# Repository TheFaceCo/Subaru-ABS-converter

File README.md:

# Subaru-ABS-converter
Read hall sensors, output variable reluctance (VR) sensors.

This converts modern hall sensor inputs to older VR outputs using a Maxim 9921 IC to read 2-wire hall sensors with a Teensy 3.2. 
Use this device if you are installing new hubs that use hall wheel speed sensors on old cars with variable reluctance ABS tone-rings.

The output stage is a 2-bit digital output fed to an audio transformer (1:1 600ohm:600ohm). 
The transformer removes the DC bias and presents an inductive source to the OEM ABS inputs (to circumvent open- or short-circuit error detection).

Set the input wheel tooth count to the OEM VR wheel tooth count. 

Set the output wheel tooth count to 2x the number of magnetic poles (count poles using magentic film, see image of subaru encoder). 
The Max9921 counts both the rising and falling edge of each magnetic pole, hence the multiplier.

Set Teensy clock to 24MHz to reduce thermal issues. CPU may freeze at high temperatures. First suspect for stability problems is the crystal oscillator. 

This also includes a generic digital output labeled "VSS". This allows the device to present a VSS signal calculated as the average of both inputs.
The VSS output can be used to provide a VSS signal in the case of a new transmission without a built-in VSS sensor.
The VSS output, as installed in my car, just drives an LED and is used for status reporting. This needs to be modified if you want a proper VSS output.

There is an additional op-amp stage, but this has been left un-routed due to pure laziness. 

This setup produces and unknown amount of jitter, but it should be relatively small. 

Outputs will be disabled by >1 error per 10 seconds in the default config. 

Be sure to cut the USB power trace on the teensy prior to soldering to the board.

Use at your own risk.

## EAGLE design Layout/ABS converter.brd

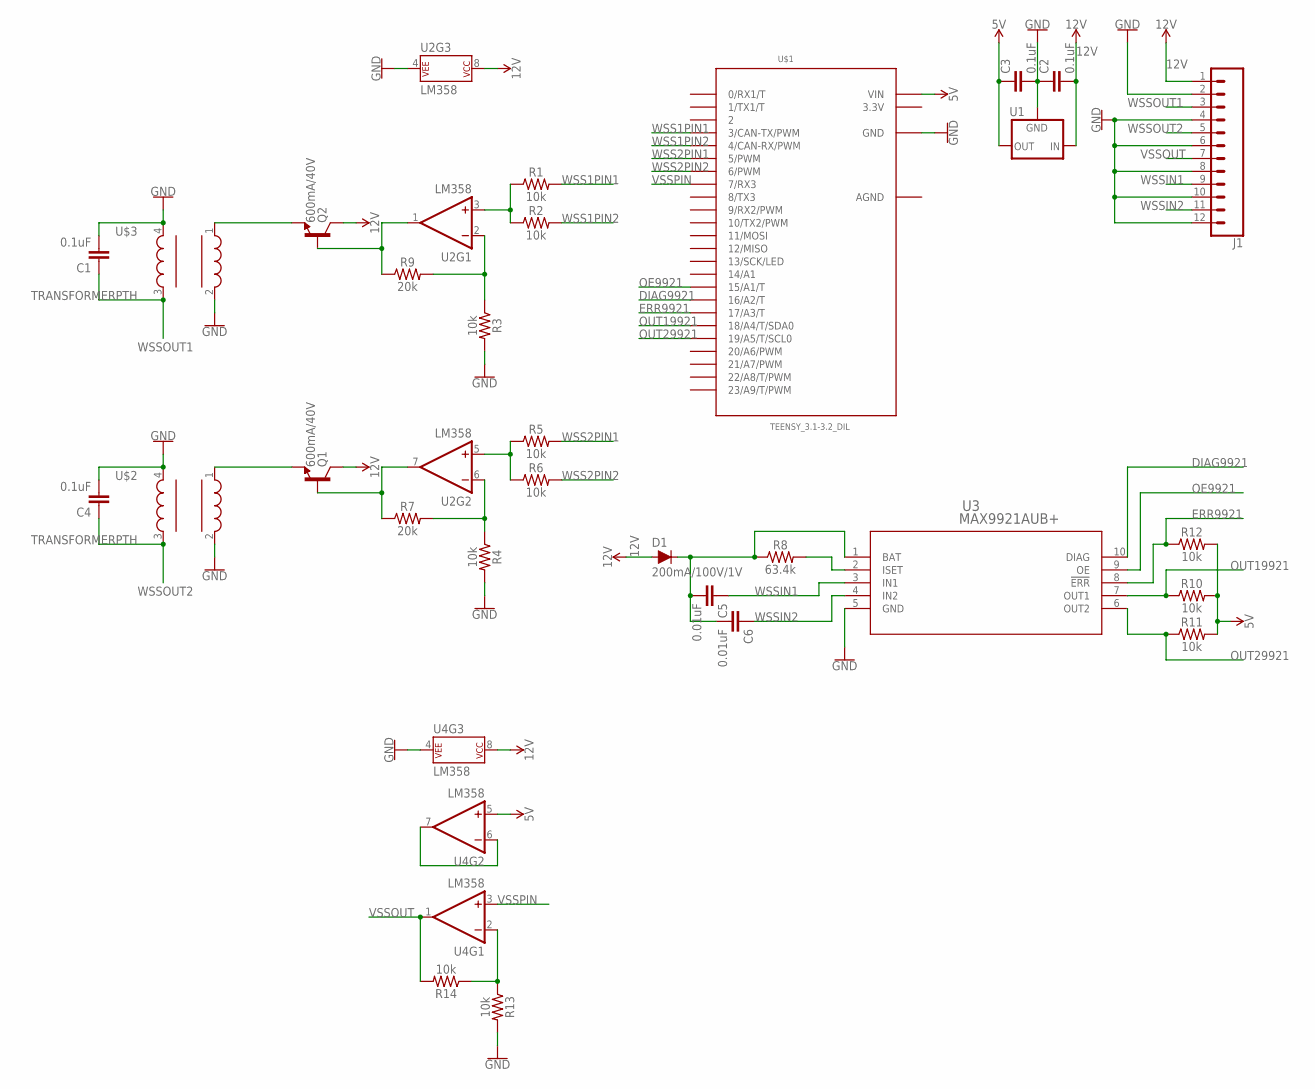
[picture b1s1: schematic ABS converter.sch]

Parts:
C1, C2, C3, C4: 0.1uF; CAP-PTH-SMALL-KIT
C5, C6: 0.01uF; CAP-PTH-SMALL-KIT
D1: 200mA/100V/1V; DIODE-1N4148
J1: CONN_12; 1X12
Q1, Q2: 600mA/40V; TO-92
R1, R2, R3, R4, R5, R6, R10, R11, R12, R13, R14: 10k; AXIAL-0.3
R7, R9: 20k; AXIAL-0.3
R8: 63.4k; AXIAL-0.3
U1: V_REG_78XX-TO-220; TO-220-ALT
U2, U4: LM358; DIP08
U3: MAX9921AUB+; 21-0061L
U$1: TEENSY_3.1-3.2_DIL; TEENSY_3.0-3.2&LC_DIL
U$2, U$3: TRANSFORMERPTH; TRANSFORMER

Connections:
3.3V: U$1.3.3V
5V: C3.1, R10.P$2 (2), R11.P$2 (2), R12.P$2 (2), U1.OUT, U4.5 (+IN), U$1.VIN
12V: C2.2, D1.A, J1.1, Q1.1 (C), Q2.1 (C), U1.IN, U2.8 (P$V+), U4.8 (P$V+)
AGND: U$1.AGND
DIAG9921: U3.10 (DIAG), U$1.16/A2 (16/A2/T)
ERR9921: R12.P$1 (1), U3.8 (!ERR), U$1.17/A3 (17/A3/T)
GND: C1.2, C2.1, C3.2, C4.2, J1.2, J1.4, J1.6, J1.8, J1.10, J1.12, R3.P$2 (2), R4.P$2 (2), R13.P$2 (2), U1.GND, U2.4 (P$V-), U3.5 (GND), U4.4 (P$V-), U$1.GND, U$2.2, U$2.4, U$3.2, U$3.4; also elsewhere on the board
unnamed: Q2.2 (B), R9.P$1 (1), U2.1 (OUT)
unnamed: R1.P$1 (1), R2.P$1 (1), U2.3 (+IN)
unnamed: R3.P$1 (1), R9.P$2 (2), U2.2 (-IN)
unnamed: Q2.3 (E), U$3.1
unnamed: R5.P$1 (1), R6.P$1 (1), U2.5 (+IN)
unnamed: R4.P$1 (1), R7.P$2 (2), U2.6 (-IN)
unnamed: Q1.2 (B), R7.P$1 (1), U2.7 (OUT)
unnamed: Q1.3 (E), U$2.1
unnamed: R8.P$2 (2), U3.2 (ISET)
unnamed 16: C5.2, C6.2, D1.C, R8.P$1 (1), U3.1 (BAT); also elsewhere on the board
unnamed: U4.6 (-IN), U4.7 (OUT)
unnamed: R13.P$1 (1), R14.P$1 (1), U4.2 (-IN)
OE9921: U3.9 (OE), U$1.15/A1 (15/A1/T)
OUT19921: R10.P$1 (1), U3.7 (OUT1), U$1.18/A4 (18/A4/T/SDA0)
OUT29921: R11.P$1 (1), U3.6 (OUT2), U$1.19/A5 (19/A5/T/SCL0)
VSSOUT: J1.7, R14.P$2 (2), U4.1 (OUT)
VSSPIN: U4.3 (+IN), U$1.7 (7/RX3)
WSS1PIN1: R1.P$2 (2), U$1.3 (3/CAN-TX/PWM)
WSS1PIN2: R2.P$2 (2), U$1.4 (4/CAN-RX/PWM)
WSS2PIN1: R5.P$2 (2), U$1.5 (5/PWM)
WSS2PIN2: R6.P$2 (2), U$1.6 (6/PWM)
WSSIN1: C5.1, J1.9, U3.3 (IN1)
WSSIN2: C6.1, J1.11, U3.4 (IN2)
WSSOUT1: C1.1, J1.3, U$3.3
WSSOUT2: C4.1, J1.5, U$2.3

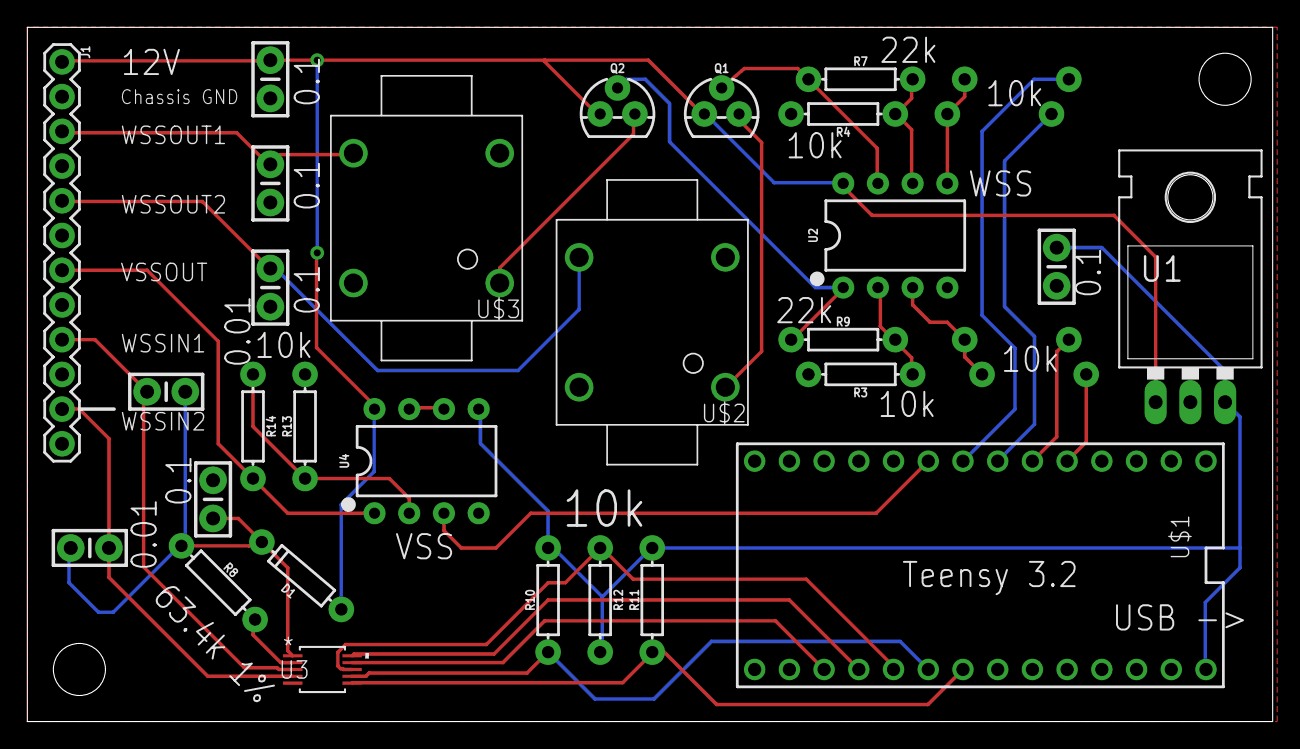
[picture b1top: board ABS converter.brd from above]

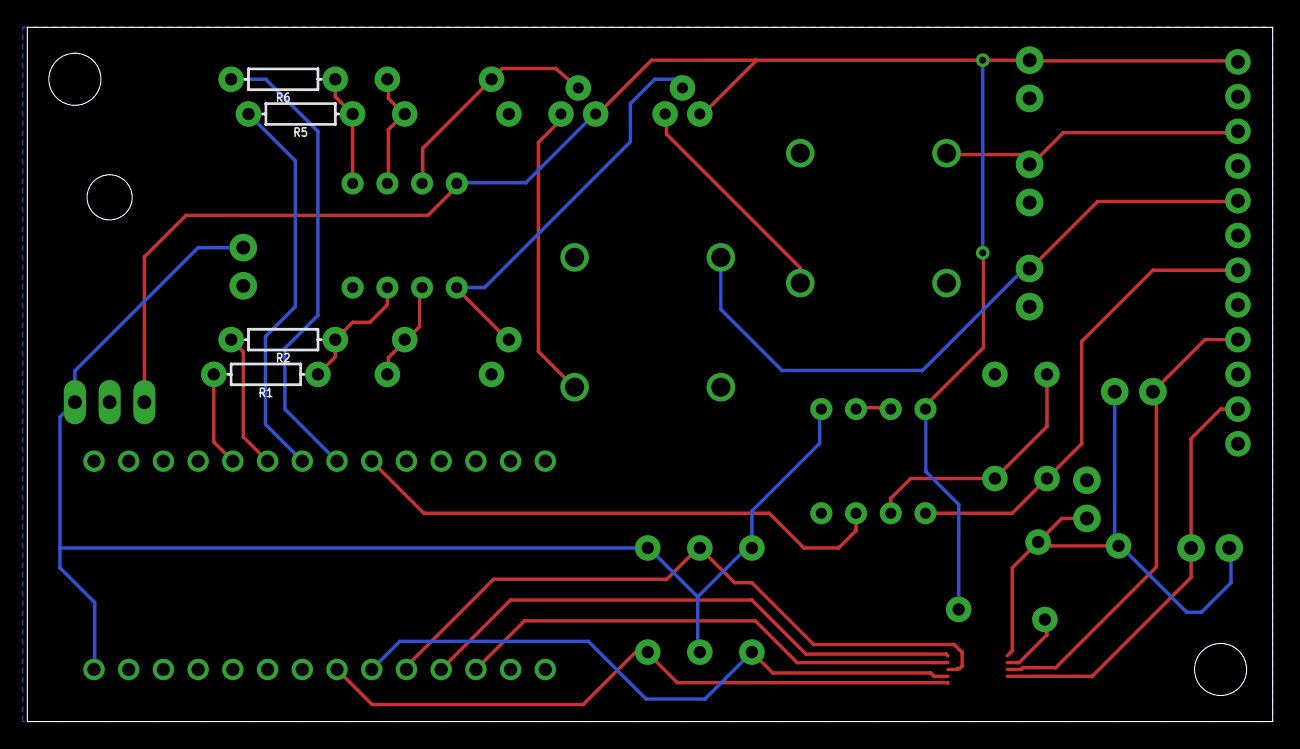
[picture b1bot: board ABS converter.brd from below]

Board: 2 copper layers, 91.1 x 50.8 mm, 32 parts (4 on the bottom side), 30 nets.

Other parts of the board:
C7: 0.1uF; CAP-PTH-SMALL-KIT

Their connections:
GND: C7.2; also elsewhere on the board
unnamed 16: C7.1; also elsewhere on the board

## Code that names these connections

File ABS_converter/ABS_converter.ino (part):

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const unsigned long outputwheelteeth = 44;
const unsigned long VSSwheelteeth = 1; //this number is made up. Set to correct wheel count from transmission

#define WSS1PIN1  3
#define WSS1PIN2  4
#define WSS2PIN1  5
#define WSS2PIN2  6
#define VSSPIN    7
#define OE9921    15
#define DIAG9921  16
#define ERR9921   17
#define OUT19921  18
#define OUT29921  19
#define ONBOARDLED 13

unsigned long halfwave = 300; //used to determined the shape of the output pulse
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
  //  }
  //wheelspeed outputs use two output pins through a voltage divider for 0, 1.75, and 3v (00, 01, and 11)
  pinMode(WSS1PIN1, OUTPUT); //wheelspeed 1 output 1
  pinMode(WSS1PIN2, OUTPUT); //wheelspeed 1 output 2
  pinMode(WSS2PIN1, OUTPUT);//wheelspeed 2 output 1
  pinMode(WSS2PIN2, OUTPUT);//wheelspeed 2 output 2

  pinMode(VSSPIN, OUTPUT);//VSS output
  pinMode(OE9921, OUTPUT);//Output enable to MAX9921
  pinMode(DIAG9921, OUTPUT);//Diag to MAX9921
  pinMode(ERR9921, INPUT); //ERR from MAX9921
  pinMode(OUT19921, INPUT); //Hall 1 signal from MAX9921
  pinMode(OUT29921, INPUT); //Hall 2 signal from MAX9921

  pinMode(ONBOARDLED, OUTPUT); //onboard LED to display power
  digitalWriteFast(ONBOARDLED, HIGH); //display power state
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
  Serial.println("Max9921 enabled");

  attachInterrupt(digitalPinToInterrupt(OUT19921), input1ISR, CHANGE); //count rising and falling edges of Max9921 outputs.
  attachInterrupt(digitalPinToInterrupt(OUT29921), input2ISR, CHANGE);
  attachInterrupt(digitalPinToInterrupt(ERR9921), ERRISR, FALLING);

  delayflag1 = micros(); //sets up initial conditions for WSS output waveform
  periodflag1 = delayflag1; //avoid second call to micros(), trickrepeated throughout
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
  VSSdelayflag = delayflag1;

  digitalWriteFast(WSS1PIN1, HIGH);
  digitalWriteFast(WSS1PIN2, LOW);
  digitalWriteFast(WSS2PIN1, HIGH);
  digitalWriteFast(WSS2PIN2, LOW);
  digitalWriteFast(VSSPIN, HIGH);

  updateVSS();
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      //    if (period1 > minimumspeed) {
      if (periodtimer1 - delayflag1 >= signal1start) {
        if (!signal1started) {
          digitalWriteFast(WSS1PIN1, LOW);
          digitalWriteFast(WSS1PIN2, LOW);
          signal1started = true;
          signal1send = signal1start + halfwave; //re-find zero crossing center in order to tolerate rapidly changing periods. If this is preloaded, signal distortion will result when the period is updated at a bad time.
          signal1end = signal1send + halfwave; //re-find waveform end (should correspond to the period on average)
        }
        if (!signal1sent) {
          if (periodtimer1 - delayflag1 >= signal1send) {
            digitalWriteFast(WSS1PIN1, HIGH);
            digitalWriteFast(WSS1PIN2, HIGH);
            signal1sent = true;
            signal1ended = false;
          }
        }
        if (!signal1ended) {
          if (periodtimer1 - delayflag1 >= signal1end) {
            digitalWriteFast(WSS1PIN1, HIGH);
            digitalWriteFast(WSS1PIN2, LOW);
            delayflag1 = periodtimer1;
            signal1ended = true;
            signal1started = false;
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      }
      //    }
      //    else {
      //      digitalWriteFast(WSS1PIN1, HIGH);
      //      digitalWriteFast(WSS1PIN2, LOW);
      //      delayflag1 = periodtimer1;
      //      signal1ended = true;
      //      signal1started = false;
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      //    if (period2 > minimumspeed) {
      if (periodtimer2 - delayflag2 >= signal2start) {
        if (!signal2started) {
          digitalWriteFast(WSS2PIN1, LOW);
          digitalWriteFast(WSS2PIN2, LOW);
          signal2started = true;
          signal2send = signal2start + halfwave; //re-find zero crossing center in order to tolerate rapidly changing periods. If this is preloaded, signal distortion will result when the period is updated at a bad time.
          signal2end = signal2send + halfwave; //re-find waveform end (should correspond to the period on average)
        }
        if (!signal2sent) {
          if (periodtimer2 - delayflag2 >= signal2send) {
            digitalWriteFast(WSS2PIN1, HIGH);
            digitalWriteFast(WSS2PIN2, HIGH);
            signal2sent = true;
            signal2ended = false;
          }
        }
        if (!signal2ended) {
          if (periodtimer2 - delayflag2 >= signal2end) {
            digitalWriteFast(WSS2PIN1, HIGH);
            digitalWriteFast(WSS2PIN2, LOW);
            delayflag2 = periodtimer2;
            signal2ended = true;
            signal2started = false;
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      }
      //    }
      //    else {
      //      digitalWriteFast(WSS2PIN1, HIGH);
      //      digitalWriteFast(WSS2PIN2, LOW);
      //      delayflag2 = periodtimer2;
      //      signal2ended = true;
      //      signal2started = false;
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    }
  }
  if (errreport > 1) { //if more than 1 error has been encountered in 10 seconds disable outputs and write error out to LED connected to VSS pin.
    detachInterrupt(digitalPinToInterrupt(ERR9921));
    disabled = true; //
    if (!VSSoutput) { //if the VSS pin is used for a status LED, use it to blink the most recent error reported by Max9921. One blink = 0, two blinks = 1
      for (int i = 0; i <= 5; i++) {
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}

void ERRISR() {
  digitalWriteFast(DIAG9921, HIGH); //drive diagnostic pin high to retreive diagnostic info. See truth table in Max9921 documentation. IN1 faults mask IN2 faults. Faults are transient (not latched), so this must be fast.
  delayMicroseconds(1); //allow a bit of time for error output. 350ns according to Max9921 documentation. This probably isn't required, but it's hard to say.
  ERRstatus = digitalReadFast(ERR9921); //Retrieve pin status
  OUT1status = digitalReadFast(OUT19921);
  OUT2status = digitalReadFast(OUT29921);
  digitalWriteFast(DIAG9921, LOW); //drive diagnostic pin low to reset faulted sensor.
  error = true;
}

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
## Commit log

2019-08-29 made a housing for it
2019-08-29 fixed component heights
2019-08-29 tooth count images
2019-08-31 added corrected tone ring tooth counts
    -
2019-09-16 fixed resistor labels
    changes to common 22k from 20k on opamps. Added big label to 63.4k resistor for max9921 chip configuration.
2019-09-16 Updated for correct pinouts
    Added temporary VSS output. Split out inputs and outputs for L/R WSS.
    Added some more labels on board and moved them around for visibility when assembled.
2019-09-17 removed input filter
    changed some other things that were inconsequential.
    ABS light goes off, but ABS is super sensitive, suggesting that the period conversion is wrong.
2019-09-17 simplified slightly
    set a couple settings back to originals
2019-09-17 set rolling average to 50/50 factors
2019-09-17 rejigger to lock out period updates during waveform generation
2019-09-18 added back in the filter, block operation until a WSS sees an input.
2019-09-18 added minimum speed to outputs
    inverted output waveform
2019-09-18 what the fuck
    inverted the tooth counts and the brakes work properly, but not with the number in the correct spot.
2019-09-20 --- This seems to work ---
    set output tooth count to 88 (presumably there is a logic inverter to get a second pulse between teeth?).
    Seems sensitive to pulsewidth. 600uS seems like a happy medium - 400 uS seems to throw a light eventually and 750uS seems to throw a light quickly.
    Changed complements to 90/10 from 50/50. Changed light timeout to 2000 pulses.
    Could change to timeout at 300,000,000uS to get a 5 minute delay or 120,000,000 to get a 2 minute delay.
    Expect extreme jitter around 90mph with this code, due to the 600uS pulse running out of time (need 425uS pulsewidth at 120mph).
2019-09-20 changed to do math all the time
    Does the period update at all times, but doesn't shunt the result into the active variable until it's outside the waveform.
    Compresses waveform to 400uS when period is less than 650uS.
2019-09-20 changed to period variable scaling
    Changed from fixed period scaling to dynamic period scaling in order to keep wavelength as long as practicable. Scaling starts around 85mph (18.9 rev/s at 808 revs/mile)
2019-09-20 Update ABS_converter.ino
    added VSS light count to declarations
2019-09-20 figured out the math problem.
    the hall sensor is probably only reading every other encoder line, due to being a 2-wire hall sensor. Need to read up on how exactly they work.
2019-09-20 fixed lack of explicit outpu on diag port
2019-09-20 regr
2019-09-20 documentation
    etc
2019-09-20 debug to verify count of 48 input teeth
    turns out alternating poles meants 96 on the magnet paper is 48 electrical.
2019-09-20 ISR's to 'change'
    The encoder alternates magnetic poles, and the max9921 interprets them as 1-0-1-0-etc. Both rising and falling edges are mechanically precise, and using both will reduce the output latency (since you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
    Filter changed to weight the previous value more heavily as a resut.
2019-09-20 Add VSS on/off selection, cleaned up variable definitions
    added filter back to VSS output.
2019-09-20 photos
2020-08-30 added diagnostic output to VSS pin
    As installed in my car, the VSS pin is being used to drive an LED. This outputs some diagnostics over the LED pin and serial.
2020-08-30 fixed delays in diag output
2020-08-31 Improved error handling.
    Prior commits did not utilize the error or diagnostics pins on the Max, and any error would blank the outputs long enough to throw an ABS error at the ECU.
    New commit will automatically reset the Max9921 after reading an error. as quickly as possible (<2uS) Multiple fast errors (10s or less between errors) will disable the output and read out the error 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
2020-08-31 Added "pending error" to output LED on VSS
    Will show a pending "CEL" (1 error in a ten second period). Clears after 10 seconds, unless another error is reported by the Max9921. If another error is found, the outputs are disabled and the last 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
    Also cleaned up comments and bracketed all the "VSS as LED output" lines so they shut off if VSS is enabled.
    debug as unsigned int for predictable wrap behavior.
2020-09-06 added longer startup delay. Added note about clock speed.
2020-09-06 Added input filter cap to Max9921
    This should have been in there from the get-go. It will hold the max up during momentary brownouts.

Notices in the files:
parts and their libraries:
SparkFun-Capacitors: Licensing: Creative Commons ShareAlike 4.0 International - https://creativecommons.org/licenses/by-sa/4.0
